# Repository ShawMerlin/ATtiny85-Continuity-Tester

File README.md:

# ATtiny85-Continuity-Tester

The lack of good quality Continuity Testers is shocking.  Even some of the more expensives ones are terrible. <br />
False Alarms and the potential of damaging sensitive equipment have to be looked at as well. <br />

I found this ATtiny Continuity Tester schematic from https://github.com/technoblogy/continuity-tester  <br /> 
Having an easy to assembly kit for DIYers was also considered in the creation of this PCB. <br />

ATtiny85 Program Code can be found here:  http://www.technoblogy.com/list?1ZNS <br />

It is set to go into sleep mode after 1 minute to save battery power. <br />
in Sleep Mode, the LED will be powered off and will wake again when the leads touch. <br /> 
A power switch was also included so that it can be stored for longer periods of time. <br />

Not wanting to replace batteries often, I included a dual 18650 holder that has both batteries in parallel. <br />
The 18650 Batteries will literally self-discharge before being used up by this circuit.  <br />

Project is completely open source with Kicad files to be provided.  This can be modified to your hears desire. <br />

More Content Like this - www.facebook.com/GeekIslandGaming  <br />

All Donations are reinvested into ideas and projects. Thank you for the support!! <br /> <br />

Here is a blown up picture of this board with things removed to make it easier to see what parts go where. <br />

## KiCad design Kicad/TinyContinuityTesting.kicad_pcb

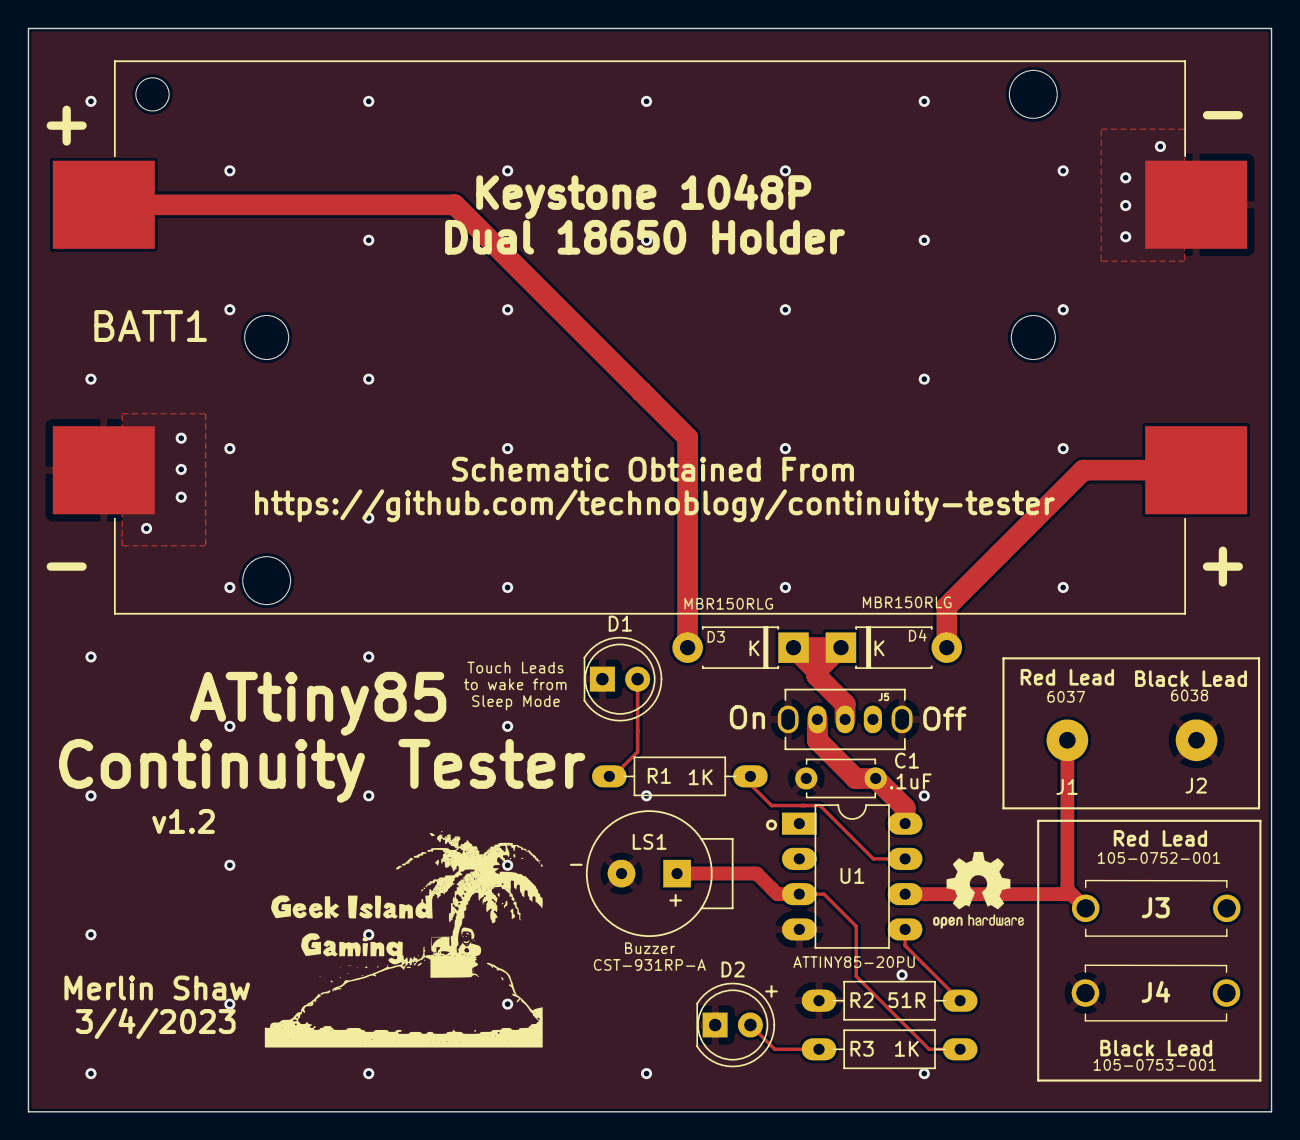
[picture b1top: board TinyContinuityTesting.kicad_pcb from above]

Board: 2 copper layers, 89.5 x 78.0 mm, 16 parts (0 on the bottom side), 10 nets.

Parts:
BATT1: BAT_1048P
C1: .1uF; C_Disc_D4.7mm_W2.5mm_P5.00mm
D1, D2: LED_D5.0mm
D3, D4: D_DO-41_SOD81_P7.62mm_Horizontal
J1, J2: PinHeader_1x01_P2.54mm_Vertical
J3: Probe; 1050752001
J4: Gnd; 1050752001
J5: Conn_01x03; SW_OS102011MS2QN1
LS1: Buzzer_CUI_CST-931RP-A
R1, R3: 2.7K; R_Axial_DIN0207_L6.3mm_D2.5mm_P10.16mm_Horizontal
R2: 51R; R_Axial_DIN0207_L6.3mm_D2.5mm_P10.16mm_Horizontal
U1: ATtiny85-20S; DIP-8_W7.62mm

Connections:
3V: C1.1, J5.1, U1.8 (VCC)
22: D1.2 (A), R1.1
333: D3.1, D4.1, J5.2
+3.3V: D3.2, D4.2
GND: BATT1.1-, BATT1.2-, C1.2, D1.1 (K), D2.1 (K), J2.1, J4.1, LS1.M, R2.1, U1.4 (GND)
unnamed: D2.2 (A), R3.2
unnamed: J1.1, J3.1, U1.6 (PB1)
unnamed: R2.2, U1.5 (AREF/PB0)
unnamed: R1.2, U1.7 (PB2)
unnamed: LS1.P, R3.1, U1.3 (XTAL2/PB4)
